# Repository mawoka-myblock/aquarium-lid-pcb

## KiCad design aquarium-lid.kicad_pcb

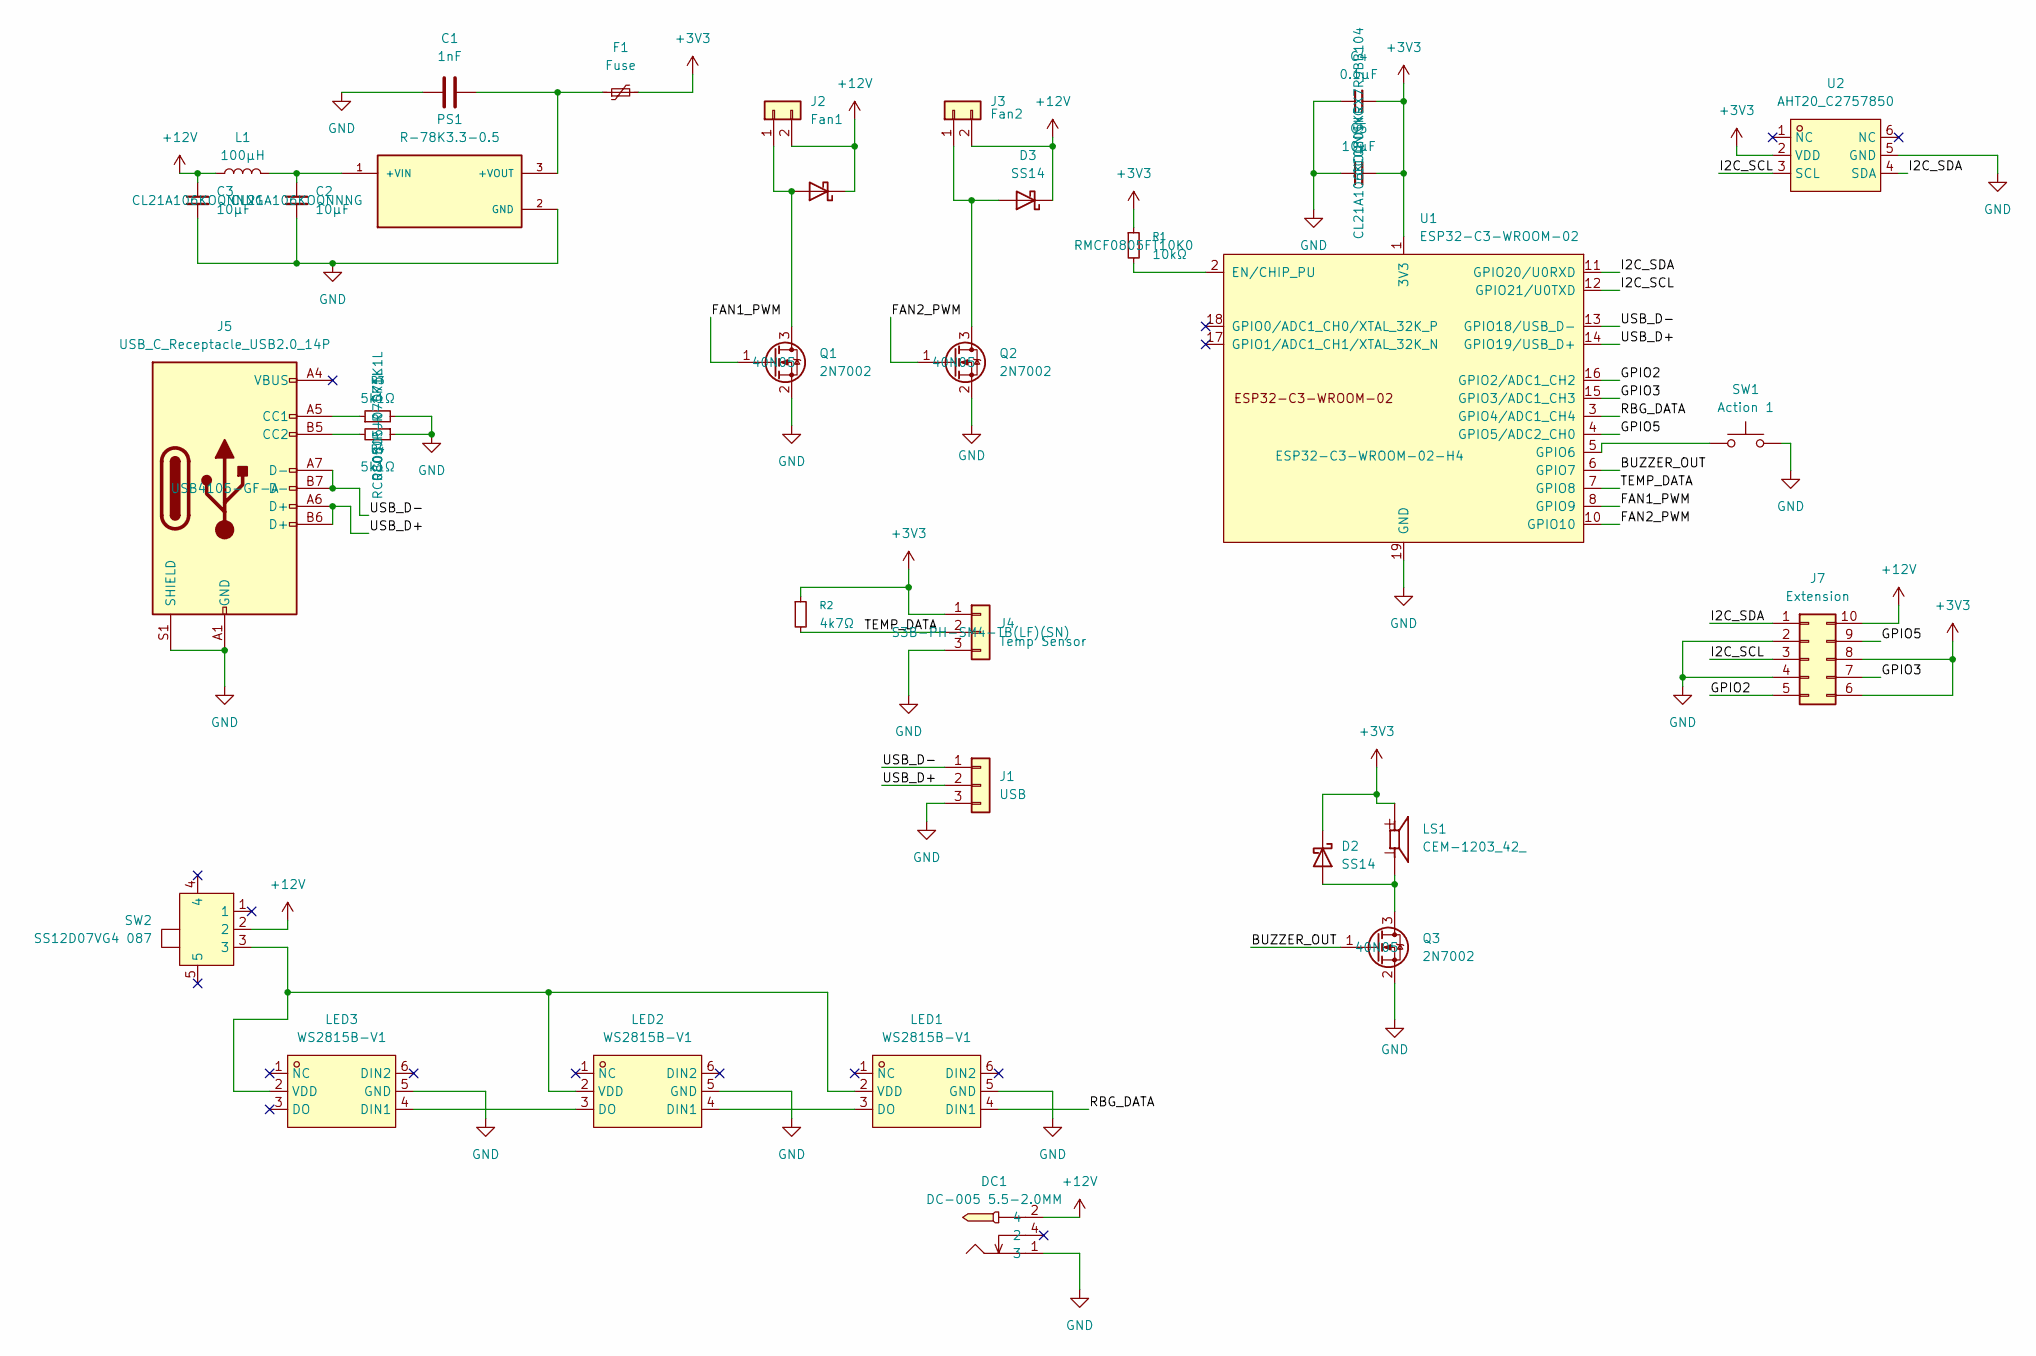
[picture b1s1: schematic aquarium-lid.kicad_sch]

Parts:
C1: 1nF; C_0805_2012Metric
C2, C3, C5: 10µF; C_0805_2012Metric
C4: 0.1µF; C_0805_2012Metric
D2, D3, D4: SS14; D_SMA
DC1: DC-005 5.5-2.0MM; DC-IN-TH_DC-5520-1; LCSC Part C16214
F1: Fuse; Fuse_1206_3216Metric
J1: USB; PinHeader_1x03_P2.54mm_Vertical
J2: Fan1; JST_XH_S2B-XH-A-1_1x02_P2.50mm_Horizontal
J3: Fan2; JST_XH_S2B-XH-A-1_1x02_P2.50mm_Horizontal
J4: Temp Sensor; JST_PH_S3B-PH-SM4-TB_1x03-1MP_P2.00mm_Horizontal
J5: USB_C_Receptacle_USB2.0_14P; USB_C_Receptacle_GCT_USB4105-xx-A_16P_TopMnt_Horizontal
J7: Extension; PinHeader_2x05_P2.54mm_Vertical
L1: 100µH; IND-SMD_L7.8-W7.0-A
LED1, LED2, LED3: WS2815B-V1; LED-SMD_6P-L5.0-W5.0-P1.60-LS5.4-BR; LCSC Part C5446699
LS1: CEM-1203_42_; CUI_CEM-1203_42_
PS1: R-78K3.3-0.5; CONV_R-78K3.3-0.5; PARTREV 0/2023
Q1, Q2, Q3: 2N7002; SOT-23
R1: 10kΩ; R_0805_2012Metric
R2: 4k7Ω; R_0805_2012Metric
R3, R4: 5k1Ω; R_0805_2012Metric
SW1: Action 1; SW_TS04-66-43-BK-100-SMT
SW2: SS12D07VG4 087; SW-TH_SS12D07VG4; LCSC Part C2939726
U1: ESP32-C3-WROOM-02
U2: AHT20_C2757850; SENSOR-SMD_L3.0-W3.0-P1.00-BR; LCSC Part C2757850

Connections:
+3V3: C4.2, C5.2, D2.1 (K), F1.2, J4.1, J7.6, J7.8, LS1.P, R1.1, R2.1, U1.1 (3V3), U2.2 (VDD)
+12V: C3.1, D3.1 (K), D4.1 (K), DC1.2 (4), J2.2, J3.2, J7.10, L1.1, SW2.2
/BUZZER_OUT: Q3.1 (G), U1.6 (GPIO7)
/FAN1_PWM: Q1.1 (G), U1.8 (GPIO9)
/FAN2_PWM: Q2.1 (G), U1.10 (GPIO10)
/GPIO2: J7.5, U1.16 (GPIO2/ADC1_CH2)
/GPIO3: J7.7, U1.15 (GPIO3/ADC1_CH3)
/GPIO5: J7.9, U1.4 (GPIO5/ADC2_CH0)
/I2C_SCL: J7.3, U1.12 (GPIO21/U0TXD), U2.3 (SCL)
/I2C_SDA: J7.1, U1.11 (GPIO20/U0RXD), U2.4 (SDA)
/RBG_DATA: LED1.4 (DIN1), U1.3 (GPIO4/ADC1_CH4)
/TEMP_DATA: J4.2, R2.2, U1.7 (GPIO8)
/USB_D+: J1.2, J5.A6 (D+), J5.B6 (D+), U1.14 (GPIO19/USB_D+)
/USB_D-: J1.1, J5.A7 (D-), J5.B7 (D-), U1.13 (GPIO18/USB_D-)
GND: C1.1, C2.2, C3.2, C4.1, C5.1, DC1.1 (3), J1.3, J4.3, J5.A1 (GND), J5.A12 (GND), J5.B1 (GND), J5.B12 (GND), J5.S1 (SHIELD), J7.2, J7.4, LED1.5 (GND), LED2.5 (GND), LED3.5 (GND), PS1.2 (GND), Q1.2 (S), Q2.2 (S), Q3.2 (S), R3.2, R4.1, SW1.2, U1.9 (GND), U1.19 (GND), U2.5 (GND)
unnamed: D2.2 (A), LS1.N, Q3.3 (D)
unnamed: D3.2 (A), J3.1, Q2.3 (D)
unnamed: D4.2 (A), J2.1, Q1.3 (D)
unnamed: J5.A5 (CC1), R3.1
unnamed: J5.B5 (CC2), R4.2
unnamed: LED1.3 (DO), LED2.4 (DIN1)
unnamed: LED1.2 (VDD), LED2.2 (VDD), LED3.2 (VDD), SW2.3
unnamed: LED2.3 (DO), LED3.4 (DIN1)
unnamed: C2.1, L1.2, PS1.1 (+VIN)
unnamed: C1.2, F1.1, PS1.3 (+VOUT)
unnamed: R1.2, U1.2 (EN/CHIP_PU)
unnamed: SW1.1, U1.5 (GPIO6)

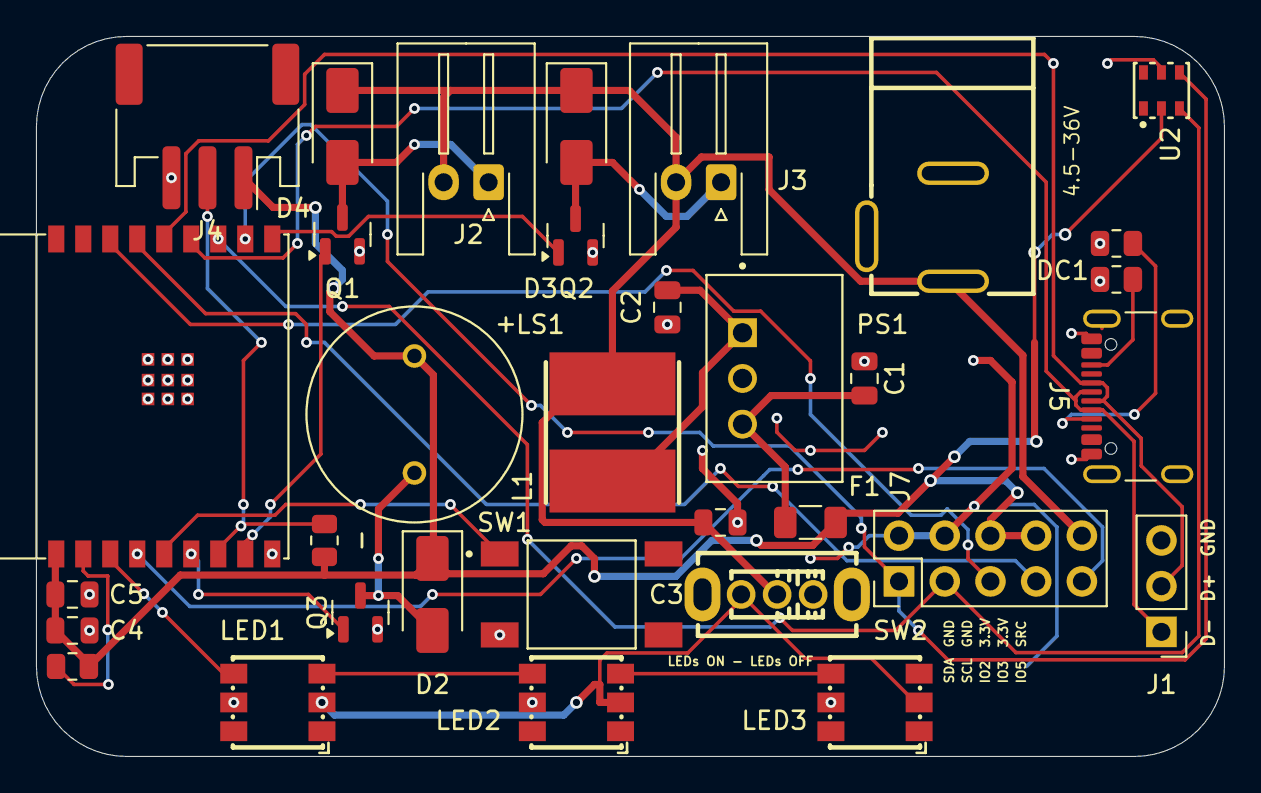
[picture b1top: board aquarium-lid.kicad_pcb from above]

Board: 2 copper layers, 66.0 x 40.0 mm, 33 parts (0 on the bottom side), 27 nets.

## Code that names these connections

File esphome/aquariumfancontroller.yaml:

substitutions:
  name: aquariumfancontroller
  friendly_name: Aquarium Fan Controller

esphome:
  name: "${name}"
  friendly_name: "${friendly_name}"
  name_add_mac_suffix: True
  project:
    name: esphome.aquarium-fan-controller
    version: "0.1"

dashboard_import:
  package_import_url: github://mawoka-myblock/aquarium-lid-pcb/esphome/aquariumfancontroller.yaml

esp32:
  board: esp32-c3-devkitm-1
  framework:
    type: arduino

# Enable logging
logger:

ota:
  - platform: esphome
api:
wifi:
  ap:
    password: "mawoka.eu"

improv_serial:

captive_portal:
esp32_improv:
  authorizer: none

script:
  - id: play_siren_loop
    mode: restart
    then:
      - while:
          condition:
            lambda: return id(alarm_triggered) && !id(alarm_silenced);
          then:
            - rtttl.play: "siren:d=8,o=5,b=100:d,e,d,e,d,e,d,e"
            - delay: 2.8s
  - id: trigger_alarm
    parameters:
      is_high_alarm: bool
    then:
      - if:
          condition:
            lambda: return !id(alarm_triggered);
          then:
            - globals.set:
                id: alarm_triggered
                value: "true"
            - globals.set:
                id: alarm_silenced
                value: "false"
            - globals.set:
                id: is_hot_alarm
                value: !lambda return is_high_alarm;
            - script.execute: play_siren_loop
            - light.turn_on:
                id: leds
                effect: "Alarm Strobe"
  - id: disable_alarm
    then:
      - if:
          condition:
            lambda: return id(alarm_triggered);
          then:
            - globals.set:
                id: alarm_triggered
                value: "false"
            - globals.set:
                id: alarm_silenced
                value: "false"
            - rtttl.stop
            - lambda: |-
                auto call = id(leds).turn_on();
                auto name = to_string((int) id(led_standby_brightness).state) + "% Pulse";
                call.set_effect(name);
                call.perform();

fan:
  - platform: speed
    output: fan1_out
    id: fan1
    name: Fan 1
    web_server:
      sorting_group_id: sg_manual_control
  - platform: speed
    output: fan2_out
    id: fan2
    name: Fan 2
    web_server:
      sorting_group_id: sg_manual_control

binary_sensor:
  - platform: gpio
    pin:
      number: GPIO6
      mode:
        pullup: True
        input: True
      inverted: True
    name: Button
    on_click:
      - min_length: 1500ms
        max_length: 5s
        then:
          - if:
              condition:
                lambda: return id(alarm_silenced);
              then:
                - globals.set:
                    id: alarm_silenced
                    value: "false"
                - if:
                    condition:
                      lambda: return id(alarm_triggered);
                    then:
                      - script.execute: play_siren_loop
                      - rtttl.stop
              else:
                - globals.set:
                    id: alarm_silenced
                    value: "true"
    web_server:
      sorting_group_id: sg_status
  - platform: template
    name: "Alarm triggered"
    lambda: return id(alarm_triggered);
    web_server:
      sorting_group_id: sg_status

globals:
  - id: alarm_triggered
    type: bool
    initial_value: "false"
  - id: alarm_silenced
    type: bool
    initial_value: "false"
  - id: is_hot_alarm
    type: bool
    initial_value: "false"

output:
  - platform: ledc
    id: fan1_out
    pin: GPIO9
  - platform: ledc
    id: fan2_out
    pin: GPIO10
  - platform: ledc
    id: buzzer
    pin: GPIO7

rtttl:
  - output: buzzer

light:
  - platform: esp32_rmt_led_strip
    num_leds: 3
    pin: GPIO4
    rgb_order: GRB
    name: LEDs
    id: leds
    rmt_channel: 0
    bit0_high: 300ns
    bit1_high: 600ns
    bit0_low: 2000ns
    bit1_low: 2000ns
    restore_mode: RESTORE_DEFAULT_ON
    effects:
      - addressable_rainbow:
      - strobe:
          name: "Alarm Strobe"
          colors:
            - state: true
              brightness: 100%
              red: 100%
              green: 0%
              blue: 0%
              duration: 1s
            - state: false
              duration: 1s

      - pulse:
          name: 10% Pulse
          transition_length: 3s
          update_interval: 3s
          max_brightness: 10%
      - pulse:
          name: 30% Pulse
          transition_length: 3s
          update_interval: 3s
          max_brightness: 30%
      - pulse:
          name: 60% Pulse
          transition_length: 3s
          update_interval: 3s
          max_brightness: 60%
      - pulse:
          name: 100% Pulse
          transition_length: 3s
          update_interval: 3s
          max_brightness: 100%
    web_server:
      sorting_group_id: sg_manual_control

web_server:
  port: 80
  version: 3
  log: false
  sorting_groups:
    - id: sg_settings
      name: Settings
    - id: sg_status
      name: Status
    - id: sg_manual_control
      name: Manual Control
  local: true

one_wire:
  - platform: gpio
    pin: GPIO8

i2c:
  sda: GPIO20
  scl: GPIO21

sensor:
  - platform: dallas_temp
    name: Temperature
    update_interval: 10s
    on_value:
      then:
        - if:
            condition:
              lambda: "return id(fan_on_temp).state < x;"
            then:
              - fan.turn_on:
                  id: fan1
                  speed: 100
              - fan.turn_on:
                  id: fan2
                  speed: 100
            else:
              - fan.turn_off: fan1
              - fan.turn_off: fan2
        - if:
            condition:
              lambda: "return id(alarm_high_temp).state < x;"
            then:
              - script.execute:
                  id: trigger_alarm
                  is_high_alarm: "true"
            else:
              - if:
                  condition:
                    lambda: "return id(alarm_low_temp).state > x;"
                  then:
                    - script.execute:
                        id: trigger_alarm
                        is_high_alarm: "true"
                  else:
                    - script.execute: disable_alarm
    web_server:
      sorting_group_id: sg_status
  - platform: aht10
    variant: AHT20
    temperature: 
      name: Aquarium External Temperature
    humidity: 
      name: Aquarium External Humidity

number:
  - platform: template
    name: Fan On Temperature
    optimistic: true
    id: fan_on_temp
    min_value: 18
    max_value: 40
    step: 0.1
    unit_of_measurement: °C
    restore_value: True
    web_server:
      sorting_group_id: sg_settings
  - platform: template
    name: "Alarm High Temp"
    id: alarm_high_temp
    optimistic: true
    min_value: 15
    max_value: 45
    step: 0.1
    unit_of_measurement: "°C"
    restore_value: True
    web_server:
      sorting_group_id: sg_settings
  - platform: template
    name: "Alarm Low Temp"
    id: alarm_low_temp
    optimistic: true
    min_value: 0
    max_value: 30
    step: 0.1
    unit_of_measurement: "°C"
    restore_value: True
    web_server:
      sorting_group_id: sg_settings
  - platform: template
    name: "LED Standby Brightness"
    id: led_standby_brightness
    optimistic: true
    min_value: 10
    max_value: 100
    step: 10
    restore_value: True
    web_server:
      sorting_group_id: sg_settings

select:
  - platform: template
    name: LED Standby Mode
    id: led_standby_mode
    optimistic: true
    options:
      - "Color Breathing"
      - "Off"
      - "Constant Color"
      - Rainbow
    web_server:
      sorting_group_id: sg_settings

switch:
  - platform: template
    name: "Enable Moisture Blast"
    id: moisture_blast
    optimistic: true
    web_server:
      sorting_group_id: sg_manual_control
  - platform: template
    name: "Silence Alarm"
    lambda: return id(alarm_silenced);
    turn_on_action:
      then:
        - globals.set:
            id: alarm_silenced
            value: "true"
    turn_off_action:
      then:
        - globals.set:
            id: alarm_silenced
            value: "false"
        - if:
            condition:
              lambda: return id(alarm_triggered);
            then:
              - script.execute: play_siren_loop
              - rtttl.stop
    web_server:
      sorting_group_id: sg_manual_control

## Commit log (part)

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2025-06-03 Quick save
2025-06-20 New PCB
2025-06-26 PCB updates
2025-07-11 Add manual control and .1 degree turns fans off
2025-10-09 Bump slab from 0.4.10 to 0.4.11 in /backend
    Bumps [slab](https://github.com/tokio-rs/slab) from 0.4.10 to 0.4.11.
    - [Release notes](https://github.com/tokio-rs/slab/releases)
    - [Changelog](https://github.com/tokio-rs/slab/blob/master/CHANGELOG.md)
    - [Commits](https://github.com/tokio-rs/slab/compare/v0.4.10...v0.4.11)
    ---
    updated-dependencies:
2025-10-09 Bump tracing-subscriber from 0.3.19 to 0.3.20 in /backend
    Bumps [tracing-subscriber](https://github.com/tokio-rs/tracing) from 0.3.19 to 0.3.20.
    - [Release notes](https://github.com/tokio-rs/tracing/releases)
    - [Commits](https://github.com/tokio-rs/tracing/compare/tracing-subscriber-0.3.19...tracing-subscriber-0.3.20)
    ---
    updated-dependencies:
    - dependency-name: tracing-subscriber
2026-01-08 Bump salvo from 0.80.0 to 0.88.1 in /backend
    Bumps [salvo](https://github.com/salvo-rs/salvo) from 0.80.0 to 0.88.1.
    - [Release notes](https://github.com/salvo-rs/salvo/releases)
    - [Commits](https://github.com/salvo-rs/salvo/compare/v0.80.0...v0.88.1)
    ---
    updated-dependencies:
    - dependency-name: salvo
2026-02-03 Bump bytes from 1.10.1 to 1.11.1 in /backend
    Bumps [bytes](https://github.com/tokio-rs/bytes) from 1.10.1 to 1.11.1.
    - [Release notes](https://github.com/tokio-rs/bytes/releases)
    - [Changelog](https://github.com/tokio-rs/bytes/blob/master/CHANGELOG.md)
    - [Commits](https://github.com/tokio-rs/bytes/compare/v1.10.1...v1.11.1)
    ---
    updated-dependencies:
2026-03-11 Bump quinn-proto from 0.11.12 to 0.11.14 in /backend
    Bumps [quinn-proto](https://github.com/quinn-rs/quinn) from 0.11.12 to 0.11.14.
    - [Release notes](https://github.com/quinn-rs/quinn/releases)
    - [Commits](https://github.com/quinn-rs/quinn/compare/quinn-proto-0.11.12...quinn-proto-0.11.14)
    ---
    updated-dependencies:
    - dependency-name: quinn-proto
2026-03-19 Bump salvo from 0.80.0 to 0.89.3 in /backend
    Bumps [salvo](https://github.com/salvo-rs/salvo) from 0.80.0 to 0.89.3.
    - [Release notes](https://github.com/salvo-rs/salvo/releases)
    - [Commits](https://github.com/salvo-rs/salvo/compare/v0.80.0...v0.89.3)
    ---
    updated-dependencies:
    - dependency-name: salvo
2026-03-21 Bump rustls-webpki from 0.103.4 to 0.103.10 in /backend
    Bumps [rustls-webpki](https://github.com/rustls/webpki) from 0.103.4 to 0.103.10.
    - [Release notes](https://github.com/rustls/webpki/releases)
    - [Commits](https://github.com/rustls/webpki/compare/v/0.103.4...v/0.103.10)
    ---
    updated-dependencies:
    - dependency-name: rustls-webpki
2026-05-01 :sparkles: Huge progess
2026-05-01 MQTT Progress
2026-05-01 save
2026-05-01 Progress
2026-05-01 Add mqtt
2026-05-05 Cleanup and working LEDC
2026-05-08 progress on buzzer
2026-05-09 :sparkles: Better mqtt and working alarm
2026-05-10 :sparkles: Added working web interface
2026-05-10 :sparkles: Add workflow
2026-05-10 :bug: Fix workflow (1)
2026-05-10 :bug: Fix workflow (2)
2026-05-10 Approve esbuild build script
2026-05-10 Run build on branch main
2026-05-10 Update to use http git
2026-05-10 Build on firmware change
2026-05-10 Make CI run on nightly
2026-05-10 Allow esbuild buildscript
2026-05-10 Fix pnpm ci command
2026-05-10 Fix workflows
2026-05-10 Possibly fix rust caching error
2026-05-10 Restructure to cargo workspace
2026-05-10 Resolve stale clippy warning
2026-05-10 Add button action
2026-05-14 Add garbage collection to invalidate_key
2026-06-21 Improve error handling
2026-06-21 Fix unused import
2026-06-21 Format code
2026-06-27 Add rounding to Water Temperature in MQTT
